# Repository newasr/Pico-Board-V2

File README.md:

# Pico-Board-V2
PICO Board v1 : [Github Link](http://github.com/newasr/Pico-board)

Changes:
- Resolved DRC and ERC which were there in v1.
- Added the Raspberry Pi logo for a more authentic look.
- Standardized component names to be horizontally aligned for a cleaner and more readable design.

# Schematic

# 3D View

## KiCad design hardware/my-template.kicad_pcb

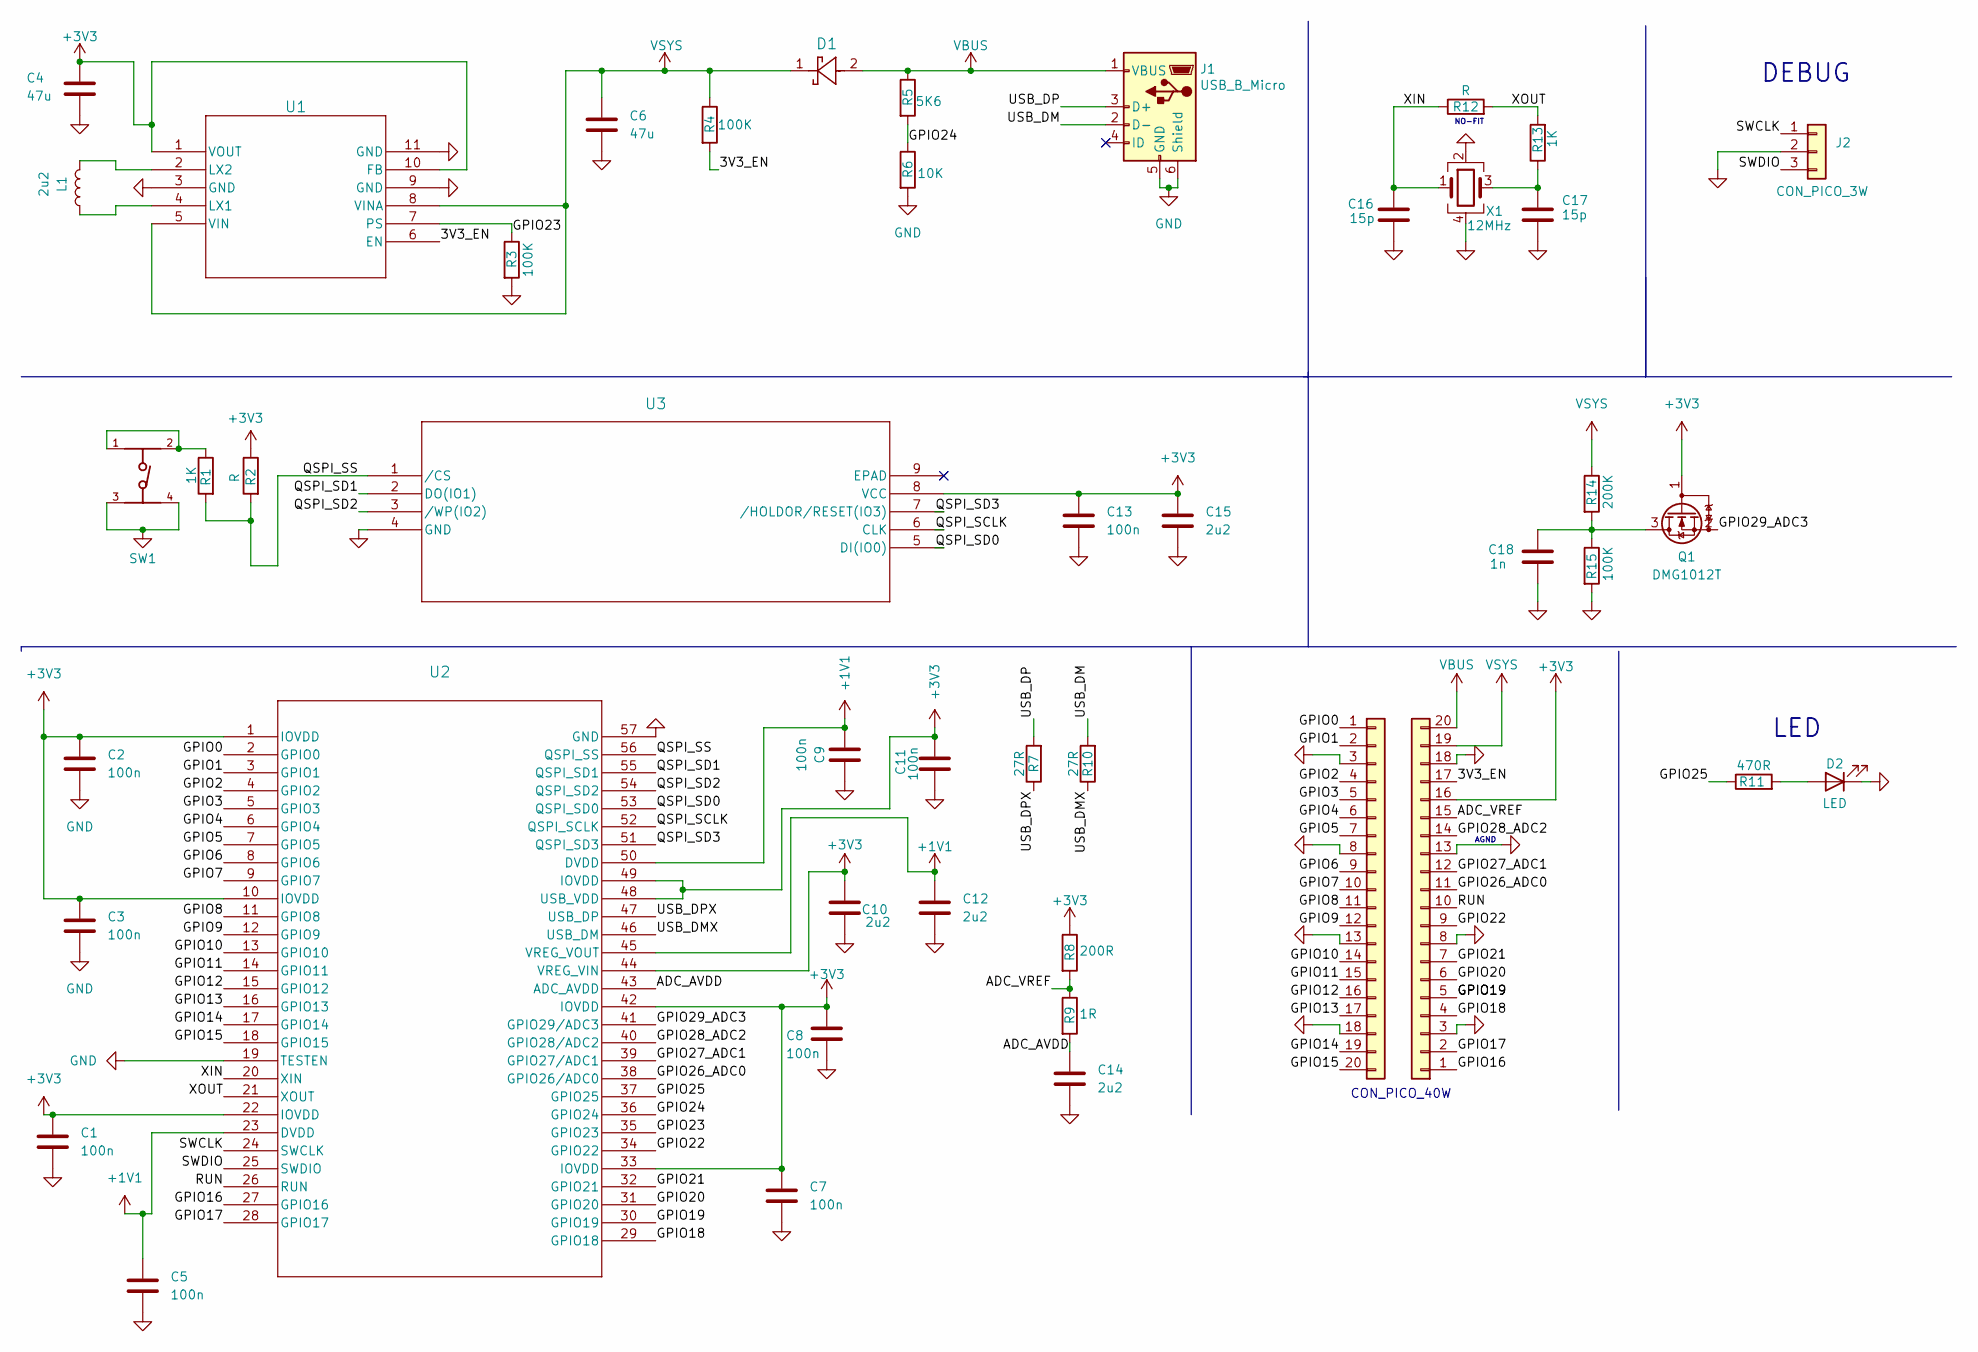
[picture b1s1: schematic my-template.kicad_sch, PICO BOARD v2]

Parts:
C1, C2, C3, C5, C7, C8, C9, C11, C13: 100n; C_0201_0603Metric; Digikey Part# CL03A104KQ3NNNC
C4, C6: 47u; C_0805_2012Metric; Digikey Part# CL21A476MQYNNNE
C10, C12, C14, C15: 2u2; C_0402_1005Metric; Digikey Part# CL05A225MQ5NNNC
C16, C17: 15p; C_0201_0603Metric; Digikey Part# GRM0335C1E150JA01D
C18: 1n; C_0201_0603Metric; Digikey Part# KGM05AR70J102MH
D1: MBR120VLSFT1G; Digikey Part# MBR120VLSFT1G
D2: LED; LED_0402_1005Metric; Digikey Part# 150040GS73240
J1: USB_B_Micro; USB_Micro-B_Molex_47346-0001; Digikey Part# 0473460001
J2: CON_PICO_3W; 3_pin_connector
J3: Conn_01x20; part_1_40_pin
J4: Conn_01x20; part_2_40_pin
L1: 2u2; L_0402_1005Metric; Digikey Part# MLZ1005M2R2WT000
Q1: DMG1012T; SOT-523; Digikey Part# DMG1012T-7
R1, R13: 1K; R_0402_1005Metric; Digikey Part# RK73H1ETTP1001F
R2, R12: R; R_0402_1005Metric
R3, R4, R15: 100K; R_0402_1005Metric; Digikey Part# RK73H1ETTP1003F
R5: 5K6; R_0402_1005Metric; Digikey Part# ERJ-2RKF5601X
R6: 10K; R_0402_1005Metric; Digikey Part# RK73H1ETTP1002F
R7, R10: 27R; R_0201_0603Metric; Digikey Part# RK73H1ETTP27R0F
R8: 200R; R_0603_1608Metric; Digikey Part# CRCW0603200RFKEAC
R9: 1R; R_0402_1005Metric; Digikey Part# RK73H1ETTP1R00F
R11: 470R; R_0402_1005Metric; Digikey Part# RK73H1ETTP4700F
R14: 200K; R_0402_1005Metric; Digikey Part# RK73H1ETTP2003F
SW1: 434133025816; PART-NUMBER 434133025816; Digikey Part# 434133025816
U1: RT6150B-33GQW; Digikey Part# RT6150B-33GQW
U2: SC09147; QFN56_7X7_RPI; Digikey Part# SC0914(7)
U3: W25Q16JVUXIQ TR; W25Q16JVUXIQ_TR; Digikey Part# W25Q16JVUXIQ TR
X1: 12MHz; Oscillator_SMD_SeikoEpson_SG210-4Pin_2.5x2.0mm; Digikey Part# ECS-2520MVLC-120-CN-TR

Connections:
+1V1: C5.1, C9.2, C12.1, U2.23 (DVDD), U2.45 (VREG_VOUT), U2.50 (DVDD)
+3V3: C1.1, C2.1, C3.1, C4.1, C7.1, C8.1, C10.1, C11.1, C13.1, C15.1, J4.16, Q1.1 (G), R2.1, R8.1, U1.1 (VOUT), U1.10 (FB), U2.1 (IOVDD), U2.10 (IOVDD), U2.22 (IOVDD), U2.33 (IOVDD), U2.42 (IOVDD), U2.44 (VREG_VIN), U2.48 (USB_VDD), U2.49 (IOVDD), U3.8 (VCC); also elsewhere on the board
/3V3_EN: J4.17, R4.2, U1.6 (EN); also elsewhere on the board
/ADC_AVDD: C14.1, R9.2, U2.43 (ADC_AVDD)
/ADC_VREF: J4.15, R8.2, R9.1; also elsewhere on the board
/GPIO0: J3.1, U2.2 (GPIO0); also elsewhere on the board
/GPIO1: J3.2, U2.3 (GPIO1); also elsewhere on the board
/GPIO2: J3.4, U2.4 (GPIO2); also elsewhere on the board
/GPIO3: J3.5, U2.5 (GPIO3); also elsewhere on the board
/GPIO4: J3.6, U2.6 (GPIO4); also elsewhere on the board
/GPIO5: J3.7, U2.7 (GPIO5); also elsewhere on the board
/GPIO6: J3.9, U2.8 (GPIO6); also elsewhere on the board
/GPIO7: J3.10, U2.9 (GPIO7); also elsewhere on the board
/GPIO8: J3.11, U2.11 (GPIO8); also elsewhere on the board
/GPIO9: J3.12, U2.12 (GPIO9); also elsewhere on the board
/GPIO10: J3.14, U2.13 (GPIO10); also elsewhere on the board
/GPIO11: J3.15, U2.14 (GPIO11); also elsewhere on the board
/GPIO12: J3.16, U2.15 (GPIO12); also elsewhere on the board
/GPIO13: J3.17, U2.16 (GPIO13); also elsewhere on the board
/GPIO14: J3.19, U2.17 (GPIO14); also elsewhere on the board
/GPIO15: J3.20, U2.18 (GPIO15); also elsewhere on the board
/GPIO16: J4.1, U2.27 (GPIO16); also elsewhere on the board
/GPIO17: J4.2, U2.28 (GPIO17); also elsewhere on the board
/GPIO18: J4.4, U2.29 (GPIO18); also elsewhere on the board
/GPIO19: J4.5, U2.30 (GPIO19); also elsewhere on the board
/GPIO20: J4.6, U2.31 (GPIO20); also elsewhere on the board
/GPIO21: J4.7, U2.32 (GPIO21); also elsewhere on the board
/GPIO22: J4.9, U2.34 (GPIO22); also elsewhere on the board
/GPIO23: R3.1, U1.7 (PS), U2.35 (GPIO23)
/GPIO24: R5.2, R6.1, U2.36 (GPIO24)
/GPIO25: R11.1, U2.37 (GPIO25)
/GPIO26_ADC0: J4.11, U2.38 (GPIO26/ADC0); also elsewhere on the board
/GPIO27_ADC1: J4.12, U2.39 (GPIO27/ADC1); also elsewhere on the board
/GPIO28_ADC2: J4.14, U2.40 (GPIO28/ADC2); also elsewhere on the board
/GPIO29_ADC3: Q1.2 (S), U2.41 (GPIO29/ADC3)
/QSPI_SCLK: U2.52 (QSPI_SCLK), U3.6 (CLK)
/QSPI_SD0: U2.53 (QSPI_SD0), U3.5 (DI(IO0))
/QSPI_SD1: U2.55 (QSPI_SD1), U3.2 (DO(IO1))
/QSPI_SD2: U2.54 (QSPI_SD2), U3.3 (/WP(IO2))
/QSPI_SD3: U2.51 (QSPI_SD3), U3.7 (/HOLDOR/RESET(IO3))
/QSPI_SS: R1.2, R2.2, U2.56 (QSPI_SS), U3.1 (/CS)
/RUN: J4.10, U2.26 (RUN); also elsewhere on the board
/SWCLK: J2.1, U2.24 (SWCLK)
/SWDIO: J2.3, U2.25 (SWDIO)
/USB_DM: J1.2 (D-), R10.2
/USB_DMX: R10.1, U2.46 (USB_DM)
/USB_DP: J1.3 (D+), R7.2
/USB_DPX: R7.1, U2.47 (USB_DP)
/XIN: C16.1, R12.1, U2.20 (XIN), X1.1
/XOUT: R12.2, R13.2, U2.21 (XOUT)
GND: C1.2, C2.2, C3.2, C4.2, C5.2, C6.2, C7.2, C8.2, C9.1, C10.2, C11.2, C12.2, C13.2, C14.2, C15.2, C16.2, C17.2, C18.2, D2.1 (K), J1.5 (GND), J1.6 (Shield), J2.2, J3.3, J3.8, J3.13, J3.18, J4.3, J4.8, J4.13, J4.18, R3.2, R6.2, R15.2, SW1.3, SW1.4, U1.3 (GND), U1.9 (GND), U1.11 (GND), U2.19 (TESTEN), U2.57 (GND), U3.4 (GND), X1.2, X1.4; also elsewhere on the board
unnamed: C17.1, R13.1, X1.3
unnamed: D2.2 (A), R11.2
unnamed: C18.1, Q1.3 (D), R14.2, R15.1
unnamed: R1.1, SW1.1, SW1.2
unnamed: L1.1, U1.4 (LX1)
unnamed: L1.2, U1.2 (LX2)
VBUS: D1.2, J1.1 (VBUS), J4.20, R5.1; also elsewhere on the board
VSYS: C6.1, D1.1, J4.19, R4.1, R14.1, U1.5 (VIN), U1.8 (VINA); also elsewhere on the board

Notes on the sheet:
LED
CON_PICO_40W
AGND
DEBUG
NO-FIT

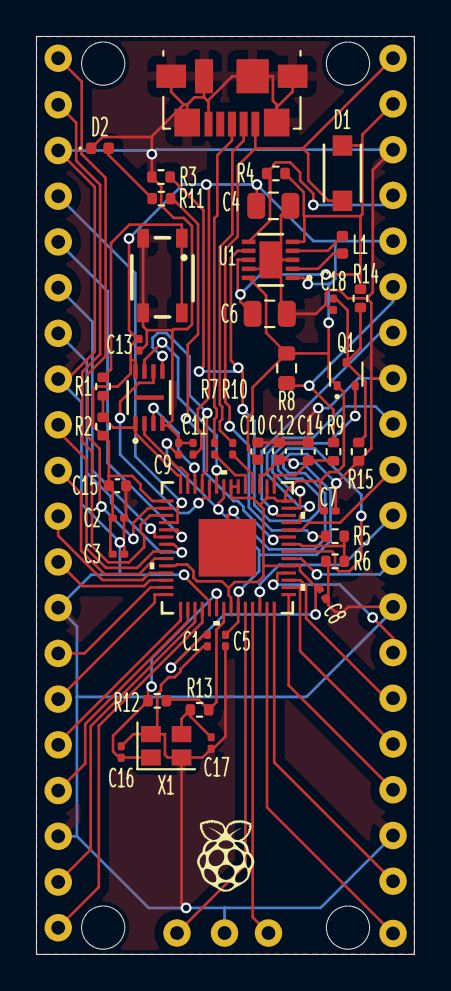
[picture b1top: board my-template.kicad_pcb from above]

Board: 2 copper layers, 21.0 x 51.0 mm, 46 parts (0 on the bottom side), 59 nets.

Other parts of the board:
40_part1: Conn_01x20; part_1_40_pin
40_part2: Conn_01x20; part_2_40_pin

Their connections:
+3V3: 40_part2.16; also elsewhere on the board
/3V3_EN: 40_part2.17; also elsewhere on the board
/ADC_VREF: 40_part2.15; also elsewhere on the board
/GPIO0: 40_part1.1; also elsewhere on the board
/GPIO1: 40_part1.2; also elsewhere on the board
/GPIO2: 40_part1.4; also elsewhere on the board
/GPIO3: 40_part1.5; also elsewhere on the board
/GPIO4: 40_part1.6; also elsewhere on the board
/GPIO5: 40_part1.7; also elsewhere on the board
/GPIO6: 40_part1.9; also elsewhere on the board
/GPIO7: 40_part1.10; also elsewhere on the board
/GPIO8: 40_part1.11; also elsewhere on the board
/GPIO9: 40_part1.12; also elsewhere on the board
/GPIO10: 40_part1.14; also elsewhere on the board
/GPIO11: 40_part1.15; also elsewhere on the board
/GPIO12: 40_part1.16; also elsewhere on the board
/GPIO13: 40_part1.17; also elsewhere on the board
/GPIO14: 40_part1.19; also elsewhere on the board
/GPIO15: 40_part1.20; also elsewhere on the board
/GPIO16: 40_part2.1; also elsewhere on the board
/GPIO17: 40_part2.2; also elsewhere on the board
/GPIO18: 40_part2.4; also elsewhere on the board
/GPIO19: 40_part2.5; also elsewhere on the board
/GPIO20: 40_part2.6; also elsewhere on the board
/GPIO21: 40_part2.7; also elsewhere on the board
/GPIO22: 40_part2.9; also elsewhere on the board
/GPIO26_ADC0: 40_part2.11; also elsewhere on the board
/GPIO27_ADC1: 40_part2.12; also elsewhere on the board
/GPIO28_ADC2: 40_part2.14; also elsewhere on the board
/RUN: 40_part2.10; also elsewhere on the board
GND: 40_part1.3, 40_part1.8, 40_part1.13, 40_part1.18, 40_part2.3, 40_part2.8, 40_part2.13, 40_part2.18; also elsewhere on the board
VBUS: 40_part2.20; also elsewhere on the board
VSYS: 40_part2.19; also elsewhere on the board

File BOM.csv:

References,Value,Footprint,Quantity
"C1, C2, C3, C5, C7, C8, C9, C11, C13",100n,C_0201_0603Metric,9
"C10, C12, C14, C15",2u2,C_0402_1005Metric,4
"C4, C6",47u,C_0805_2012Metric,2
"C16, C17",15p,C_0201_0603Metric,2
C18,1n,C_0201_0603Metric,1
"R3, R4, R15",100K,R_0402_1005Metric,3
"R1, R13",1K,R_0402_1005Metric,2
"R2, R12",R,R_0402_1005Metric,2
"R7, R10",27R,R_0201_0603Metric,2
R5,5K6,R_0402_1005Metric,1
R6,10K,R_0402_1005Metric,1
R8,200R,R_0603_1608Metric,1
R9,1R,R_0402_1005Metric,1
R11,470R,R_0402_1005Metric,1
R14,200K,R_0402_1005Metric,1
L1,2u2,L_0402_1005Metric,1
D1,MBR120VLSFT1G,MBR120VLSFT1G,1
D2,LED,LED_0402_1005Metric,1
U1,RT6150B-33GQW,RT6150B-33GQW,1
U2,SC09147,QFN56_7X7_RPI,1
U3,W25Q16JVUXIQ TR,W25Q16JVUXIQ_TR,1
X1,12MHz,Oscillator_SMD_SeikoEpson_SG210-4Pin_2.5x2.0mm,1
SW1,434133025816,434133025816,1
40_part1,Conn_01x20,part_1_40_pin,1
40_part2,Conn_01x20,part_2_40_pin,1
Q1,DMG1012T,SOT-523,1
J1,USB_B_Micro,USB_Micro-B_Molex_47346-0001,1
J2,CON_PICO_3W,3_pin_connector,1

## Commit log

2025-02-16 Update README.md
    added initial readme
2025-02-16 Create 3d-models
2025-03-23 added schematic and 3d images
2025-03-23 added hardware files and bom
